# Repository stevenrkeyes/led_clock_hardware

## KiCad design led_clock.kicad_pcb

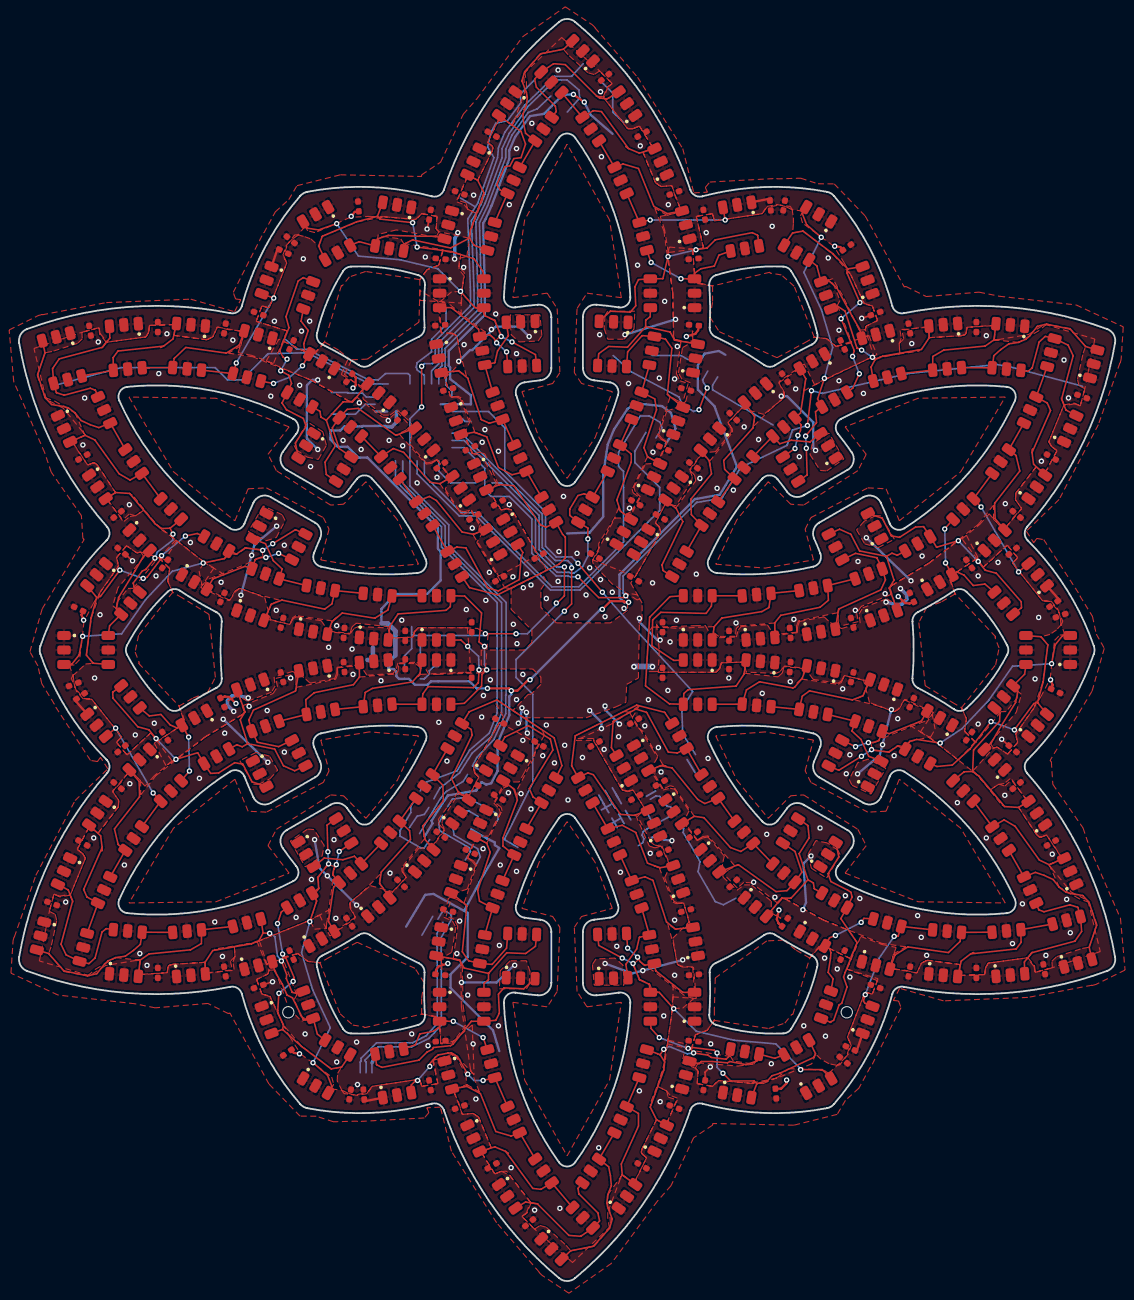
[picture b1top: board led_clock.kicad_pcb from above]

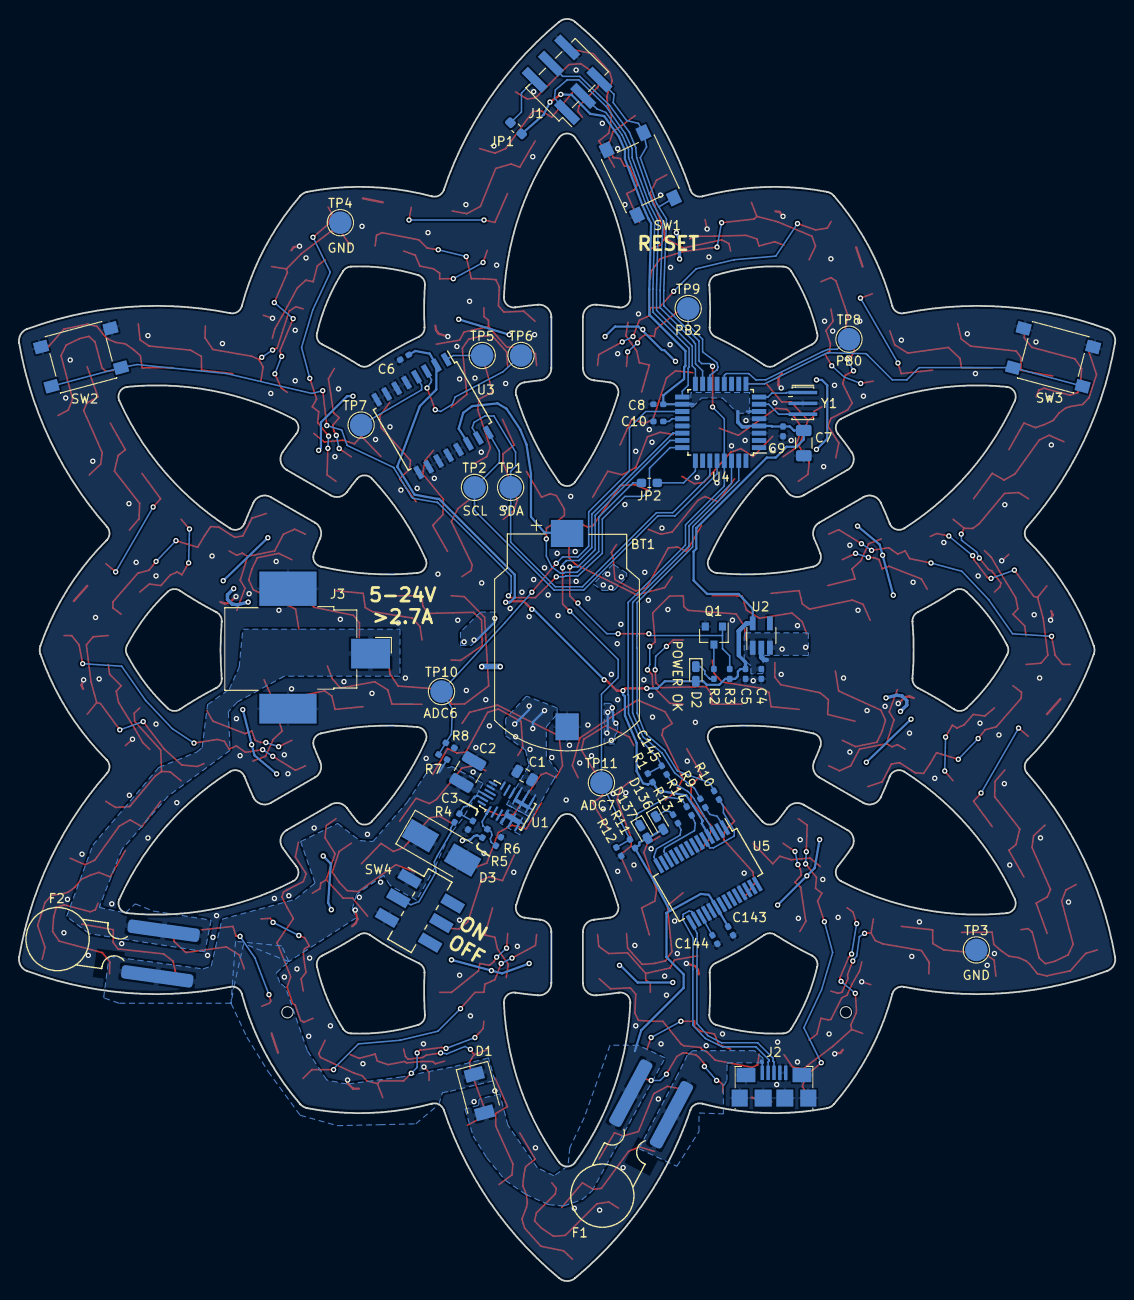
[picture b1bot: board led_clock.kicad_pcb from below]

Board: 2 copper layers, 121.3 x 139.7 mm, 328 parts (62 on the bottom side), 178 nets.

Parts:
BT1: CR2032 Battery; BatteryHolder_Harwin_S8421-45R_1x2032
C1: 22u; C_0805_2012Metric
C2: 10u; C_1210_3225Metric
C3: 100n; C_0402_1005Metric_HandSoldering
C4, C5, C6, C8, C9: 1uF; C_0402_1005Metric_HandSoldering
C7: 4.7uF Tantalum; C_1206_3216Metric
C10, C11, C12, C13, C14, C15, C16, C17, C18, C19, C20, C21, C22, C23, C24, C25, C26, C27, C28, C29, C30, C31, C32, C33, C34, C35, C36, C37, C38, C39, C40, C41, C42, C43, C44, C45, C46, C47, C48, C49, C50, C51, C52, C53, C54, C55, C56, C57, C58, C59, C60, C61, C62, C63, C64, C65, C66, C67, C68, C69, C70, C71, C72, C73, C74, C75, C76, C77, C78, C79, C80, C81, C82, C83, C84, C85, C86, C87, C88, C89, C90, C91, C92, C93, C94, C95, C96, C97, C98, C99, C100, C101, C102, C103, C104, C105, C106, C107, C108, C109, C110, C111, C112, C113, C114, C115, C116, C117, C118, C119, C120, C121, C122, C123, C124, C125, C126, C127, C128, C129, C130, C131, C132, C133, C134, C135, C136, C137, C138, C139, C140, C141, C142, C143, C144, C145: 100nF; C_0402_1005Metric_HandSoldering
D1: D_Schottky; D_SOD-128
D2: WHITE; LED_0603_1608Metric_Castellated
D3: TVS; D_SMB_Handsoldering
D4, D5, D6, D7, D8, D9, D10, D11, D12, D13, D14, D15, D16, D17, D18, D19, D20, D21, D22, D23, D24, D25, D26, D27, D28, D29, D30, D31, D32, D33, D34, D35, D36, D37, D38, D39, D40, D41, D42, D43, D44, D45, D46, D47, D48, D49, D50, D51, D52, D53, D54, D55, D56, D57, D58, D59, D60, D61, D62, D63, D64, D65, D66, D67, D68, D69, D70, D71, D72, D73, D74, D75, D76, D77, D78, D79, D80, D81, D82, D83, D84, D85, D86, D87, D88, D89, D90, D91, D92, D93, D94, D95, D96, D97, D98, D99, D100, D101, D102, D103, D104, D105, D106, D107, D108, D109, D110, D111, D112, D113, D114, D115, D116, D117, D118, D119, D120, D121, D122, D123, D124, D125, D126, D127, D128, D129, D130, D131, D132, D133, D134, D135: WS2813; LED_WS2813_PLCC6_5.0x5.0mm_P1.6mm_Modified
D136: RED; LED_0603_1608Metric_Castellated
D137: GREEN; LED_0603_1608Metric_Castellated
F1, F2: PTC; Fuse_BelFuse_0ZRG0155FF_SMD_Modified
H2, H3: MountingHole; MandalaMountingHole
J1: Programming (ICSP); PinHeader_2x03_P2.54mm_Vertical_SMD
J2: USB_B_Micro; USB_Micro-B_Amphenol_10118192-0001LF_HandSoldering
J3: Barrel_Jack; BarrelJack_Switchcraft_RASM722-SMT_Horizontal
JP1, JP2: Jumper; R_0603_1608Metric_Pad1.05x0.95mm_HandSolder
Q1: 2N7002; SOT-23
R1, R9, R10: 1k; R_0402_1005Metric_HandSoldering
R2: 270; R_0402_1005Metric_HandSoldering
R3: 100k; R_0402_1005Metric_HandSoldering
R4: 220k; R_0402_1005Metric_HandSoldering
R5: 107 1%; R_0402_1005Metric_HandSoldering
R6: 34.0 1%; R_0402_1005Metric_HandSoldering
R7, R12: 825k 1%; R_0402_1005Metric_HandSoldering
R8: 107k 1%; R_0402_1005Metric_HandSoldering
R11: 464k 1%; R_0402_1005Metric_HandSoldering
R13, R14: 1K; R_0402_1005Metric_HandSoldering
SW1, SW2, SW3: SW_Push; SW_SPST_PTS645
SW4: SW_SPDT; SW_SPDT_CK_JS202011SCQN
TP1, TP2, TP3, TP4, TP5, TP6, TP7, TP8, TP9, TP10, TP11: TestPoint; TestPoint_Pad_D2.5mm
U1: MPM3620A; MPM3620A_HandSoldering
U2: TLV70032_SOT23-5; SOT-23-5_HandSoldering
U3: DS3231M; SOIC-16W_7.5x10.3mm_P1.27mm
U4: ATmega328P-AU; TQFP-32_7x7mm_P0.8mm
U5: FT232RL; SSOP-28_5.3x10.2mm_P0.65mm
Y1: 16MHz; Resonator_SMD_muRata_CSTxExxV-3Pin_3.0x1.1mm_HandSoldering

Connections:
/LED Chain/LED Arm 2/BIN: D13.3, D14.4, D15.6
/LED Chain/LED Arm 2/DIN: D14.3, D15.4, D16.6
/LED Chain/LED Arm 3/BIN: D24.3, D25.4, D26.6
/LED Chain/LED Arm 3/DIN: D25.3, D26.4, D27.6
/LED Chain/LED Arm 4/BIN: D35.3, D36.4, D37.6
/LED Chain/LED Arm 4/DIN: D36.3, D37.4, D38.6
/LED Chain/LED Arm 5/BIN: D46.3, D47.4, D48.6
/LED Chain/LED Arm 5/DIN: D47.3, D48.4, D49.6
/LED Chain/LED Arm 6/BIN: D57.3, D58.4, D59.6
/LED Chain/LED Arm 6/DIN: D58.3, D59.4, D60.6
/LED Chain/LED Arm 7/BIN: D68.3, D69.4, D70.6
/LED Chain/LED Arm 7/DIN: D69.3, D70.4, D71.6
/LED Chain/LED Arm 8/BIN: D79.3, D80.4, D81.6
/LED Chain/LED Arm 8/DIN: D80.3, D81.4, D82.6
/LED Chain/LED Arm 9/BIN: D90.3, D91.4, D92.6
/LED Chain/LED Arm 9/DIN: D91.3, D92.4, D93.6
/LED Chain/LED Arm 10/BIN: D101.3, D102.4, D103.6
/LED Chain/LED Arm 10/DIN: D102.3, D103.4, D104.6
/LED Chain/LED Arm 11/BIN: D112.3, D113.4, D114.6
/LED Chain/LED Arm 11/DIN: D113.3, D114.4, D115.6
/LED Chain/LED Arm 12/BIN: D123.3, D124.4, D125.6
/LED Chain/LED Arm 12/DIN: D124.3, D125.4, D126.6
/LED Chain/LED Arm 12/PENULTIMATE_DOUT: D134.3, D135.4
/LED Chain/LED_DATA: D4.4, D4.6, D5.6, JP2.2
/Microcontroller/ADC6_VEXT_MEAS: R7.2, R8.1, TP10.1, U4.19
/Microcontroller/ADC7_VUSB_MEAS: R11.2, R12.1, TP11.1, U4.22
/Microcontroller/INPUT_BUTTON_1: SW2.2, U4.24
/Microcontroller/INPUT_BUTTON_2: SW3.2, U4.9
/Microcontroller/LED_DATA_PD6: JP2.1, U4.25
/Microcontroller/MICRO_TO_USB: R10.1, U5.5
/Microcontroller/PB0: TP8.1, U4.12
/Microcontroller/PB2: TP9.1, U4.14
/Microcontroller/PWR_LED_DISABLE: Q1.1, R3.2, U4.23
/Microcontroller/RTC_SCL: TP2.1, U3.16, U4.28
/Microcontroller/RTC_SDA: TP1.1, U3.15, U4.27
/Microcontroller/USB_TO_MICRO: R9.1, U5.1
/PROG_MISO: J1.4, U4.15
/PROG_MOSI: J1.1, U4.16
/PROG_SCK: J1.3, U4.17
/Power/POWER_ON: R4.2, SW4.2
/Real-Time Clock/RTC_32KHZ: TP5.1, U3.1
/Real-Time Clock/RTC_VBAT: BT1.1, U3.14
/Real-Time Clock/RTC_~INT~: TP6.1, U3.3
/Real-Time Clock/RTC_~RST~: TP7.1, U3.4
/USB Serial/FT232_3V3_INTERNAL: C144.1, U5.17
/USB Serial/USBD_N: J2.2, U5.16
/USB Serial/USBD_P: J2.3, U5.15
/VEXT_UNPROTECTED: F2.2, J3.1
/VUSB_UNPROTECTED: F1.1, J2.1
/~MICRO_RESET~: C145.1, J1.5, R1.2, SW1.2, U4.29
GND: BT1.2, C1.2, C2.2, C3.2, C4.2, C5.2, C6.2, C7.2, C8.2, C9.2, C10.2, C11.2, C12.2, C13.2, C14.2, C15.2, C16.2, C17.2, C18.2, C19.2, C20.2, C21.2, C22.2, C23.2, C24.2, C25.2, C26.2, C27.2, C28.2, C29.2, C30.2, C31.2, C32.2, C33.2, C34.2, C35.2, C36.2, C37.2, C38.2, C39.2, C40.2, C41.2, C42.2, C43.2, C44.2, C45.2, C46.2, C47.2, C48.2, C49.2, C50.2, C51.2, C52.2, C53.2, C54.2, C55.2, C56.2, C57.2, C58.2, C59.2, C60.2, C61.2, C62.2, C63.2, C64.2, C65.2, C66.2, C67.2, C68.2, C69.2, C70.2, C71.2, C72.2, C73.2, C74.2, C75.2, C76.2, C77.2, C78.2, C79.2, C80.2, C81.2, C82.2, C83.2, C84.2, C85.2, C86.2, C87.2, C88.2, C89.2, C90.2, C91.2, C92.2, C93.2, C94.2, C95.2, C96.2, C97.2, C98.2, C99.2, C100.2, C101.2, C102.2, C103.2, C104.2, C105.2, C106.2, C107.2, C108.2, C109.2, C110.2, C111.2, C112.2, C113.2, C114.2, C115.2, C116.2, C117.2, C118.2, C119.2, C120.2, C121.2, C122.2, C123.2, C124.2, C125.2, C126.2, C127.2, C128.2, C129.2, C130.2, C131.2, C132.2, C133.2, C134.2, C135.2, C136.2, C137.2, C138.2, C139.2, C140.2, C141.2, C142.2, C143.2, C144.2, D3.2, D4.5, D5.5, D6.5, D7.5, D8.5, D9.5, D10.5, D11.5, D12.5, D13.5, D14.5, D15.5, D16.5, D17.5, D18.5, D19.5, D20.5, D21.5, D22.5, D23.5, D24.5, D25.5, D26.5, D27.5, D28.5, D29.5, D30.5, D31.5, D32.5, D33.5, D34.5, D35.5, D36.5, D37.5, D38.5, D39.5, D40.5, D41.5, D42.5, D43.5, D44.5, D45.5, D46.5, D47.5, D48.5, D49.5, D50.5, D51.5, D52.5, D53.5, D54.5, D55.5, D56.5, D57.5, D58.5, D59.5, D60.5, D61.5, D62.5, D63.5, D64.5, D65.5, D66.5, D67.5, D68.5, D69.5, D70.5, D71.5, D72.5, D73.5, D74.5, D75.5, D76.5, D77.5, D78.5, D79.5, D80.5, D81.5, D82.5, D83.5, D84.5, D85.5, D86.5, D87.5, D88.5, D89.5, D90.5, D91.5, D92.5, D93.5, D94.5, D95.5, D96.5, D97.5, D98.5, D99.5, D100.5, D101.5, D102.5, D103.5, D104.5, D105.5, D106.5, D107.5, D108.5, D109.5, D110.5, D111.5, D112.5, D113.5, D114.5, D115.5, D116.5, D117.5, D118.5, D119.5, D120.5, D121.5, D122.5, D123.5, D124.5, D125.5, D126.5, D127.5, D128.5, D129.5, D130.5, D131.5, D132.5, D133.5, D134.5, D135.5, J1.6, J2.4, J2.5, J2.6, J3.2, J3.3, Q1.2, R6.2, R8.2, R12.2, SW1.1, SW2.1, SW3.1, SW4.3, TP3.1, TP4.1, U1.3, U1.12, U1.13, U1.14, U2.2, U3.5, U3.6, U3.7, U3.8, U3.9, U3.10, U3.11, U3.12, U3.13, U4.3, U4.5, U4.21, U5.7, U5.18, U5.19, U5.21, U5.25, Y1.2
unnamed: C3.1, R4.1, U1.17
unnamed: C10.1, U4.20
unnamed: C145.2, U5.3
unnamed: D2.1, R2.1
unnamed: D4.3, D5.4, D6.6
unnamed: D5.3, D6.4, D7.6
unnamed: D6.3, D7.4, D8.6
unnamed: D7.3, D8.4, D9.6
unnamed: D10.3, D11.4, D12.6
unnamed: D9.3, D10.4, D11.6
unnamed: D8.3, D9.4, D10.6
unnamed: D11.3, D12.4, D13.6
unnamed: D12.3, D13.4, D14.6
unnamed: D15.3, D16.4, D17.6
unnamed: D16.3, D17.4, D18.6
unnamed: D17.3, D18.4, D19.6
unnamed: D18.3, D19.4, D20.6
unnamed: D19.3, D20.4, D21.6
unnamed: D20.3, D21.4, D22.6
unnamed: D21.3, D22.4, D23.6
unnamed: D22.3, D23.4, D24.6
unnamed: D23.3, D24.4, D25.6
unnamed: D26.3, D27.4, D28.6
unnamed: D27.3, D28.4, D29.6
unnamed: D28.3, D29.4, D30.6
unnamed: D29.3, D30.4, D31.6
unnamed: D30.3, D31.4, D32.6
unnamed: D31.3, D32.4, D33.6
unnamed: D32.3, D33.4, D34.6
unnamed: D33.3, D34.4, D35.6
unnamed: D34.3, D35.4, D36.6
unnamed: D37.3, D38.4, D39.6
unnamed: D38.3, D39.4, D40.6
unnamed: D39.3, D40.4, D41.6
unnamed: D40.3, D41.4, D42.6
unnamed: D41.3, D42.4, D43.6
unnamed: D42.3, D43.4, D44.6
unnamed: D43.3, D44.4, D45.6
unnamed: D44.3, D45.4, D46.6
unnamed: D45.3, D46.4, D47.6
unnamed: D48.3, D49.4, D50.6
unnamed: D49.3, D50.4, D51.6
unnamed: D50.3, D51.4, D52.6
unnamed: D51.3, D52.4, D53.6
unnamed: D52.3, D53.4, D54.6
unnamed: D53.3, D54.4, D55.6
unnamed: D54.3, D55.4, D56.6
unnamed: D55.3, D56.4, D57.6
unnamed: D56.3, D57.4, D58.6
unnamed: D59.3, D60.4, D61.6
unnamed: D60.3, D61.4, D62.6
unnamed: D61.3, D62.4, D63.6
unnamed: D62.3, D63.4, D64.6
unnamed: D63.3, D64.4, D65.6
unnamed: D64.3, D65.4, D66.6
unnamed: D65.3, D66.4, D67.6
unnamed: D66.3, D67.4, D68.6
unnamed: D67.3, D68.4, D69.6
unnamed: D70.3, D71.4, D72.6
unnamed: D71.3, D72.4, D73.6
unnamed: D72.3, D73.4, D74.6
unnamed: D73.3, D74.4, D75.6
unnamed: D74.3, D75.4, D76.6
unnamed: D75.3, D76.4, D77.6
unnamed: D76.3, D77.4, D78.6
unnamed: D77.3, D78.4, D79.6
unnamed: D78.3, D79.4, D80.6
unnamed: D81.3, D82.4, D83.6
unnamed: D82.3, D83.4, D84.6
unnamed: D83.3, D84.4, D85.6
unnamed: D84.3, D85.4, D86.6
unnamed: D85.3, D86.4, D87.6
unnamed: D86.3, D87.4, D88.6
unnamed: D87.3, D88.4, D89.6
unnamed: D88.3, D89.4, D90.6
unnamed: D89.3, D90.4, D91.6
unnamed: D92.3, D93.4, D94.6
unnamed: D93.3, D94.4, D95.6
unnamed: D94.3, D95.4, D96.6
unnamed: D95.3, D96.4, D97.6
unnamed: D96.3, D97.4, D98.6
unnamed: D97.3, D98.4, D99.6
unnamed: D100.3, D101.4, D102.6
unnamed: D99.3, D100.4, D101.6
unnamed: D98.3, D99.4, D100.6
unnamed: D103.3, D104.4, D105.6
unnamed: D104.3, D105.4, D106.6
unnamed: D105.3, D106.4, D107.6
unnamed: D106.3, D107.4, D108.6
unnamed: D107.3, D108.4, D109.6
unnamed: D108.3, D109.4, D110.6
unnamed: D109.3, D110.4, D111.6
unnamed: D110.3, D111.4, D112.6
unnamed: D111.3, D112.4, D113.6
unnamed: D114.3, D115.4, D116.6
unnamed: D115.3, D116.4, D117.6
unnamed: D116.3, D117.4, D118.6
unnamed: D117.3, D118.4, D119.6
unnamed: D118.3, D119.4, D120.6
unnamed: D119.3, D120.4, D121.6
unnamed: D120.3, D121.4, D122.6
unnamed: D121.3, D122.4, D123.6
unnamed: D122.3, D123.4, D124.6
unnamed: D125.3, D126.4, D127.6
unnamed: D126.3, D127.4, D128.6
unnamed: D127.3, D128.4, D129.6
unnamed: D128.3, D129.4, D130.6
unnamed: D129.3, D130.4, D131.6
unnamed: D130.3, D131.4, D132.6
unnamed: D131.3, D132.4, D133.6
unnamed: D132.3, D133.4, D134.6
unnamed: D133.3, D134.4, D135.6
unnamed: D136.1, R13.1
unnamed: D137.1, R14.1
unnamed: J1.2, JP1.1
unnamed: Q1.3, R2.2
unnamed: R5.2, R6.1, U1.1
unnamed: R9.2, U4.30
unnamed: R10.2, U4.31
unnamed: R13.2, U5.14
unnamed: R14.2, U5.12
unnamed: U4.7, Y1.3
unnamed: U4.8, Y1.1
VDD_3V3: C1.1, C4.1, C11.1, C12.1, C13.1, C14.1, C15.1, C16.1, C17.1, C18.1, C19.1, C20.1, C21.1, C22.1, C23.1, C24.1, C25.1, C26.1, C27.1, C28.1, C29.1, C30.1, C31.1, C32.1, C33.1, C34.1, C35.1, C36.1, C37.1, C38.1, C39.1, C40.1, C41.1, C42.1, C43.1, C44.1, C45.1, C46.1, C47.1, C48.1, C49.1, C50.1, C51.1, C52.1, C53.1, C54.1, C55.1, C56.1, C57.1, C58.1, C59.1, C60.1, C61.1, C62.1, C63.1, C64.1, C65.1, C66.1, C67.1, C68.1, C69.1, C70.1, C71.1, C72.1, C73.1, C74.1, C75.1, C76.1, C77.1, C78.1, C79.1, C80.1, C81.1, C82.1, C83.1, C84.1, C85.1, C86.1, C87.1, C88.1, C89.1, C90.1, C91.1, C92.1, C93.1, C94.1, C95.1, C96.1, C97.1, C98.1, C99.1, C100.1, C101.1, C102.1, C103.1, C104.1, C105.1, C106.1, C107.1, C108.1, C109.1, C110.1, C111.1, C112.1, C113.1, C114.1, C115.1, C116.1, C117.1, C118.1, C119.1, C120.1, C121.1, C122.1, C123.1, C124.1, C125.1, C126.1, C127.1, C128.1, C129.1, C130.1, C131.1, C132.1, C133.1, C134.1, C135.1, C136.1, C137.1, C138.1, C139.1, C140.1, C141.1, C142.1, D4.1, D4.2, D5.1, D5.2, D6.1, D6.2, D7.1, D7.2, D8.1, D8.2, D9.1, D9.2, D10.1, D10.2, D11.1, D11.2, D12.1, D12.2, D13.1, D13.2, D14.1, D14.2, D15.1, D15.2, D16.1, D16.2, D17.1, D17.2, D18.1, D18.2, D19.1, D19.2, D20.1, D20.2, D21.1, D21.2, D22.1, D22.2, D23.1, D23.2, D24.1, D24.2, D25.1, D25.2, D26.1, D26.2, D27.1, D27.2, D28.1, D28.2, D29.1, D29.2, D30.1, D30.2, D31.1, D31.2, D32.1, D32.2, D33.1, D33.2, D34.1, D34.2, D35.1, D35.2, D36.1, D36.2, D37.1, D37.2, D38.1, D38.2, D39.1, D39.2, D40.1, D40.2, D41.1, D41.2, D42.1, D42.2, D43.1, D43.2, D44.1, D44.2, D45.1, D45.2, D46.1, D46.2, D47.1, D47.2, D48.1, D48.2, D49.1, D49.2, D50.1, D50.2, D51.1, D51.2, D52.1, D52.2, D53.1, D53.2, D54.1, D54.2, D55.1, D55.2, D56.1, D56.2, D57.1, D57.2, D58.1, D58.2, D59.1, D59.2, D60.1, D60.2, D61.1, D61.2, D62.1, D62.2, D63.1, D63.2, D64.1, D64.2, D65.1, D65.2, D66.1, D66.2, D67.1, D67.2, D68.1, D68.2, D69.1, D69.2, D70.1, D70.2, D71.1, D71.2, D72.1, D72.2, D73.1, D73.2, D74.1, D74.2, D75.1, D75.2, D76.1, D76.2, D77.1, D77.2, D78.1, D78.2, D79.1, D79.2, D80.1, D80.2, D81.1, D81.2, D82.1, D82.2, D83.1, D83.2, D84.1, D84.2, D85.1, D85.2, D86.1, D86.2, D87.1, D87.2, D88.1, D88.2, D89.1, D89.2, D90.1, D90.2, D91.1, D91.2, D92.1, D92.2, D93.1, D93.2, D94.1, D94.2, D95.1, D95.2, D96.1, D96.2, D97.1, D97.2, D98.1, D98.2, D99.1, D99.2, D100.1, D100.2, D101.1, D101.2, D102.1, D102.2, D103.1, D103.2, D104.1, D104.2, D105.1, D105.2, D106.1, D106.2, D107.1, D107.2, D108.1, D108.2, D109.1, D109.2, D110.1, D110.2, D111.1, D111.2, D112.1, D112.2, D113.1, D113.2, D114.1, D114.2, D115.1, D115.2, D116.1, D116.2, D117.1, D117.2, D118.1, D118.2, D119.1, D119.2, D120.1, D120.2, D121.1, D121.2, D122.1, D122.2, D123.1, D123.2, D124.1, D124.2, D125.1, D125.2, D126.1, D126.2, D127.1, D127.2, D128.1, D128.2, D129.1, D129.2, D130.1, D130.2, D131.1, D131.2, D132.1, D132.2, D133.1, D133.2, D134.1, D134.2, D135.1, D135.2, R5.1, U1.7-9, U2.1, U2.3
VDD_MICRO_3V2: C5.1, C6.1, C7.1, C8.1, C9.1, D2.2, JP1.2, R1.1, R3.1, U2.5, U3.2, U4.4, U4.6, U4.18, U5.4
VEXT: C2.1, D1.1, D3.1, F2.1, R7.1, SW4.1, U1.16
VUSB_5V0: C143.1, D1.2, D136.2, D137.2, F1.2, R11.1, U5.20

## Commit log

2019-03-29 Initial commit
    Schematic and layout files at stage when board was sent for manufacture.
2019-03-29 Slight cleanups to top sheet
    this commit cleans up the top sheet a little bit, so it's presentable.
2019-03-29 Add errata notes
    This commit adds errata and rework notes.
2019-03-29 Center PCB
2021-01-05 Added custom library parts
    At least some of the footprints do not have the model path set correctly, but I'm still including them here for completeness.
2021-01-05 Added standoff models
    These aren't used in the EE CAD, but they can be 3D printed and attached to the board.
